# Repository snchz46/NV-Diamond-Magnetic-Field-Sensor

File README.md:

# NV-Diamond Magnetic Field Sensor — Fraunhofer IAO

> Low-cost magnetic field sensor based on nitrogen-vacancy (NV) centers in diamond.
> A green LED excites the diamond, a BPW34 photodiode behind a red filter reads its fluorescence,
> and an ESP32-S3 detects the drop in fluorescence when a magnet approaches
> and streams the signal to a browser over its own Wi-Fi.

---

## System at a glance

<p align="left">
  
  <br><em>Browser dashboard: the signal drops each time the magnet approaches, and red lines mark the detected dips.</em>
</p>

---

## How it works

Green LED (525–532 nm) → NV diamond → red filter (650–750 nm) → BPW34 photodiode → MCP607 transimpedance amplifier → two RC low-pass stages → ADS1115 16-bit ADC → ESP32-S3 → Wi-Fi → browser

A magnet near the diamond lowers its red fluorescence (by 2–3 % in the initial evaluation), and the signal returns to its baseline when the magnet is removed. The readout is all-optical: there is no microwave excitation yet, so the sensor measures fluorescence quenching, not ODMR.

---

## Module gallery

| NV module | Optical module | Main PCB | Test bench |
|:---------:|:--------------:|:--------:|:----------:|
|  |  |  |  |
| Red filter and BPW34 photodiode | Green LED and two collimator lenses | TIA, bias switch, ADC and ESP32 sockets (3D model) | Servo-driven magnet arm |

---

## Hardware overview

| Part | Description |
| ---- | ----------- |
| **NV module** | Red filter film (650–750 nm) in front of a BPW34 PIN photodiode |
| **Optical module** | Green LED (525–532 nm) and two acrylic collimator lenses (f ≈ 30 mm) |
| **Main PCB (rev 5)** | Photodiode bias switch (0, −5 or −10 V from two cascaded LM2664 charge pumps), MCP607 transimpedance amplifier (1 MΩ ∥ 4.7 nF) with an optional non-inverting stage, two RC low-pass stages (fc ≈ 160 kHz), sockets for the ADC and the ESP32 |
| **ADS1115** | External 16-bit I²C ADC: ±0.256 V full scale, 7.8 µV per count, 860 samples/s |
| **ESP32-S3 (M5Stamp S3)** | Averaging, IIR filtering and dip detection; Wi-Fi access point, web page and WebSocket stream |
| **Sensor box** | Black PLA-CF enclosure with 1 mm walls next to the diamond and 4 mm elsewhere; all wiring inside except USB-C |
| **Test bench** | SG90 servo with a printed magnet arm for repeatable magnet passes |

---

## Schematic

Schematic V1.0 of the main PCB, rev 5 (EasyEDA, 2026-02-13). PDF: [`docs/schematic_rev5.pdf`](docs/schematic_rev5.pdf).

The manufacturing files for rev 5 (Gerber, pick-and-place and assembly BOM) are not part of this repository. The technical report lists every component with its value and purpose, and the 3D board model is in [`Design/Parts/3D_PCB5.step`](Design/Parts/3D_PCB5.step).

---

## Performance results

Measured values and design figures from the documents in [`docs/`](docs).

| Metric | Value | Conditions |
| ------ | ----- | ---------- |
| Fluorescence drop | 2–3 % | Initial evaluation: 15–30 mV drop from a 0.80–1.00 V TIA output, depending on magnet position; fully reversible |
| Control run | No measurable change | Same setup and magnet motion with the red filter but without the diamond |
| Noise at the TIA output | 0.34 mV RMS | ADS1115; 6.6 mV RMS with the ESP32 internal ADC (~19×, ≈ 26 dB) |
| ADC resolution | 16 bit, 7.8 µV per count | ADS1115 at ±0.256 V full scale (production firmware) |
| Processing rate | ~86 steps/s | 860 SPS, 10 conversions averaged per step |
| Dashboard update rate | ~22 Hz | WebSocket, every 4th step |
| Maximum dip rate | 1200 dips/min | 50 ms guard between dips |
| CSV buffer | 2000 samples (~91 s) | Ring buffer in RAM, downloadable as CSV |
| Rotation test | 61.5 rpm mean, σ = 3.9 rpm | Six dips; servo programmed for 58.6 rpm; +4.9 %, consistent with the SG90's dynamics |
| Material cost | ~20 € | Including the ADS1115 and the fabricated PCB |

<p align="left">
  
  <br><em>Repeatable fluorescence dips with the magnet moved by the servo.</em>
</p>

---

## Assembly walkthrough

|  |  |
| - | - |
|  |  |

Eight steps, about 15 minutes, no soldering. Full instructions (Rev 1.0): [`docs/Assembly_instructions.pdf`](docs/Assembly_instructions.pdf).

---

## Web dashboard

<p align="left">
  
  <br><em>Dashboard on a phone, served by the ESP32-S3 over its own Wi-Fi</em>
</p>

The production firmware opens its own Wi-Fi access point, so no router or lab network is needed. Connect a phone or laptop to the sensor's network (SSID and password are set in [`web_ui.cpp`](ESP32/ReadOut/ESP32S3%20ReadOut%20Web%20Server%20Optimized/src/web_ui.cpp)) and open `http://nv-plotter.local` or `http://192.168.10.1`.

- Live trace at ~22 Hz with detected dips marked in red
- Freeze, Clear, CSV export and baseline recalibration
- Display filter, averaging depth and detection threshold adjustable at run time, without reflashing
- Single page stored in flash (~12 KB, no CDN) with pinch and scroll zoom

---

## 3D model

Autodesk Inventor parts and assemblies are in `Design/`, STL files for printing in `Design/Print/`, and Inventor presentations with exploded views and assembly animations in `Design/Photos/`.

---

## Project structure

```text
NV-Diamond-Magnetic-Field-Sensor/
├── Design/                    # Mechanical CAD (Autodesk Inventor parts and assemblies)
│   ├── Design Photos/         # Renders, build photos, dashboard screenshots, assembly steps
│   ├── Parts/                 # Component and PCB 3D models
│   ├── Photos/                # Inventor presentations, renders, assembly animations
│   └── Print/                 # STL files for 3D printing
├── docs/                      # Report, firmware reference, quick reference, assembly instructions, schematic
└── ESP32/                     # Firmware (PlatformIO, Arduino framework)
    ├── ReadOut/
    │   ├── ESP32S3 ReadOut/                       # Base acquisition firmware
    │   ├── ESP32S3 ReadOut Web Server/            # Web interface variant
    │   ├── ESP32S3 ReadOut Web Server Optimized/  # Production firmware
    │   ├── ESP32S3 Noise Optimization/            # ADS1115 vs. internal ADC noise test
    │   └── Base.cpp, IIR_Filter.cpp, encoder.cpp  # Single-file sketches: readout, IIR filter, RPM encoder
    └── servo/servo.ino        # Servo sweep for the test bench
```

---

## Firmware

Built with **PlatformIO** (Arduino framework) for the M5Stamp S3 (`m5stack-stamps3`).

```bash
cd "ESP32/ReadOut/ESP32S3 ReadOut Web Server Optimized"
pio run --target upload
```

| Module | Role |
| ------ | ---- |
| `nv_signal` | ADS1115 acquisition, averaging, IIR filters, dip detection, RPM |
| `web_ui` | Wi-Fi access point, HTTP server, WebSocket server, mDNS |
| `web_page` | Browser app stored in flash |
| `csv_logger` | Ring buffer and CSV export |
| `main` | Main loop, decimation and dip latch |

---

## Documentation

| File | Content |
| ---- | ------- |
| [`NV_Samuel_Report.docx`](docs/NV_Samuel_Report.docx) | Technical report: ADC comparison, prototypes, measurements, component list |
| [`NV_Supplement.docx`](docs/NV_Supplement.docx) | Firmware reference: modules, signal processing, WebSocket protocol, configuration |
| [`NV_quick_reference.docx`](docs/NV_quick_reference.docx) | Quick reference: performance, parameters, endpoints |
| [`Assembly_instructions.pdf`](docs/Assembly_instructions.pdf) | Kit assembly instructions, Rev 1.0 |
| [`schematic_rev5.pdf`](docs/schematic_rev5.pdf) | Main PCB schematic, rev 5 |

---

## Next steps

- Microwave excitation for ODMR measurements
- ADS1015 for up to 3300 SPS instead of 860 SPS
- Active filters such as Sallen-Key

---

## Dependencies

| Tool | Version |
| ---- | ------- |
| Autodesk Inventor | 2024+ |
| EasyEDA | v6.5.51 |
| PlatformIO | espressif32 platform ≥ 6, Arduino framework |
| Libraries | Adafruit ADS1X15 ^2.6.0, WebSockets (links2004) ^2.4.1 |

---

## Author and credits

**Samuel Sanchez Moreno** — student research assistant (HiWi) at Fraunhofer IAO, Quantum Open Innovations, 2025–2026

- Sensor concept and optics: Quantum Open Innovations team, Fraunhofer IAO
- Readout electronics and PCB, enclosure, test bench, measurements and documentation: Samuel Sanchez Moreno
- Firmware and web dashboard: written with AI coding assistants; specified, tuned and validated on the sensor by Samuel Sanchez Moreno

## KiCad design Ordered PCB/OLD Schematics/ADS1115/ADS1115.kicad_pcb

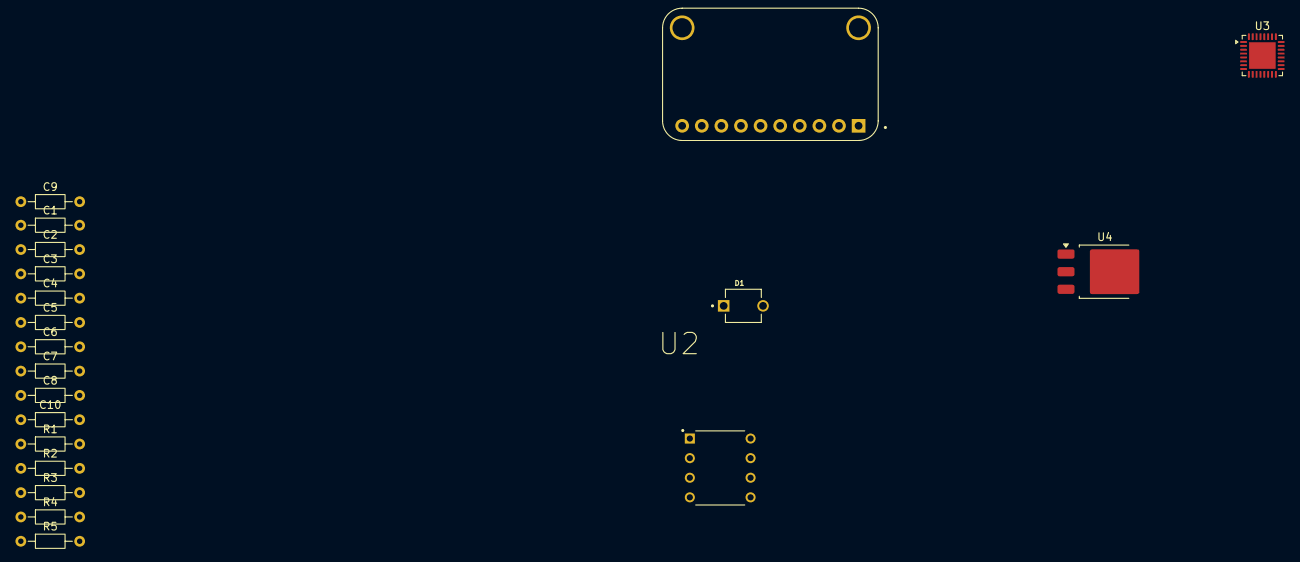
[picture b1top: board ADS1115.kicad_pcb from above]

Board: 2 copper layers, 20 parts (0 on the bottom side), 14 nets, no tracks yet.

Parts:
C1: 4n7; R_Axial_DIN0204_L3.6mm_D1.6mm_P7.62mm_Horizontal
C2, C4, C5: 10n; R_Axial_DIN0204_L3.6mm_D1.6mm_P7.62mm_Horizontal
C3: 22p; R_Axial_DIN0204_L3.6mm_D1.6mm_P7.62mm_Horizontal
C6: 1u; R_Axial_DIN0204_L3.6mm_D1.6mm_P7.62mm_Horizontal
C7, C10: 10u; R_Axial_DIN0204_L3.6mm_D1.6mm_P7.62mm_Horizontal
C8, C9: 100p; R_Axial_DIN0204_L3.6mm_D1.6mm_P7.62mm_Horizontal
D1: BPW34; DIO_BPW34
R1: 1M; R_Axial_DIN0204_L3.6mm_D1.6mm_P7.62mm_Horizontal
R2, R4: 100; R_Axial_DIN0204_L3.6mm_D1.6mm_P7.62mm_Horizontal
R3: 100k; R_Axial_DIN0204_L3.6mm_D1.6mm_P7.62mm_Horizontal
R5: 22k; R_Axial_DIN0204_L3.6mm_D1.6mm_P7.62mm_Horizontal
U1: ADS1115; MODULE_ZC261500
U2: MCP607; DIP787W46P254L927H533Q8
U3: ESP8266; QFN-32-1EP_5x5mm_P0.5mm_EP3.45x3.45mm
U4: LM1117DT-3.3; TO-252-3_TabPin2

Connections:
3V3: C5.1, C6.1, U1.10 (VDD), U2.8 (VDD), U3.3 (VDD3P3), U3.4 (VDD3P3)
+5V: C7.1, C8.1, U4.3 (VI)
GND: C2.2, C4.2, C5.2, C6.2, C7.2, C8.2, C9.2, C10.2, D1.C, R5.1, U1.6 (ADDR), U1.9 (GND), U2.3 (VINA+), U2.4 (VSS), U3.33 (GND), U4.1 (GND)
unnamed: C1.2, D1.A, R1.2, U2.2 (VINA-)
unnamed: C1.1, R1.1, R4.2, U2.1 (VOUTA)
unnamed: C3.2, R2.2, R3.1, R5.2, U2.7 (VOUTB)
unnamed: U3.1 (VDDA), U3.30 (VDDA)
unnamed: U3.11 (VDDPST), U3.17 (VDDPST)
SDA: U1.7 (SDA), U3.16 (GPIO4)
SLC: U1.8 (SCL), U3.24 (GPIO5)
TIAOut: C2.1, R2.1, U1.4 (A0)
VINB+: C4.1, R4.1, U2.5 (VINB+)
VINB-: C3.1, R3.2, U2.6 (VINB-)
VLED: C9.1, C10.1, U4.2 (VO)

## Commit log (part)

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2026-03-19 Add repository documentation structure
2026-05-08 Initial commit: NV-center readout system
2026-05-08 File system update
2026-05-08 fix: correct directory name in .gitignore for Ordered_PCB
2026-05-08 fix: add missing directory entries for Ordered PCB in .gitignore
2026-05-08 fix: remove obsolete invoice file from Ordered PCB directory
2026-05-08 Add assembly instructions, firmware documentation, and quick reference for NV-Diamond Quantum Sensor
    - Created NV_Sensor_Assembly_Instructions.docx detailing assembly steps and components for the NV-Diamond Quantum Sensor.
    - Added NV_Supplement.docx providing comprehensive firmware and software documentation, including system architecture, signal processing, and performance metrics.
    - Introduced NV_quick_reference.docx summarizing key specifications, configuration parameters, and system performance for quick access.
2026-05-08 Remove outdated schematic and project files from the repository, including NV Quenching and Samuel Quenching projects, as well as associated backups and documentation. This cleanup helps maintain a m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
2026-05-08 feat: add new design photos for NV Box and update README with enhanced project overview
2026-05-21 Add assembly instructions PDF to documentation
2026-05-21 feat: update assembly walkthrough with new images for clearer instructions
2026-05-21 feat: enhance assembly walkthrough layout for improved clarity
